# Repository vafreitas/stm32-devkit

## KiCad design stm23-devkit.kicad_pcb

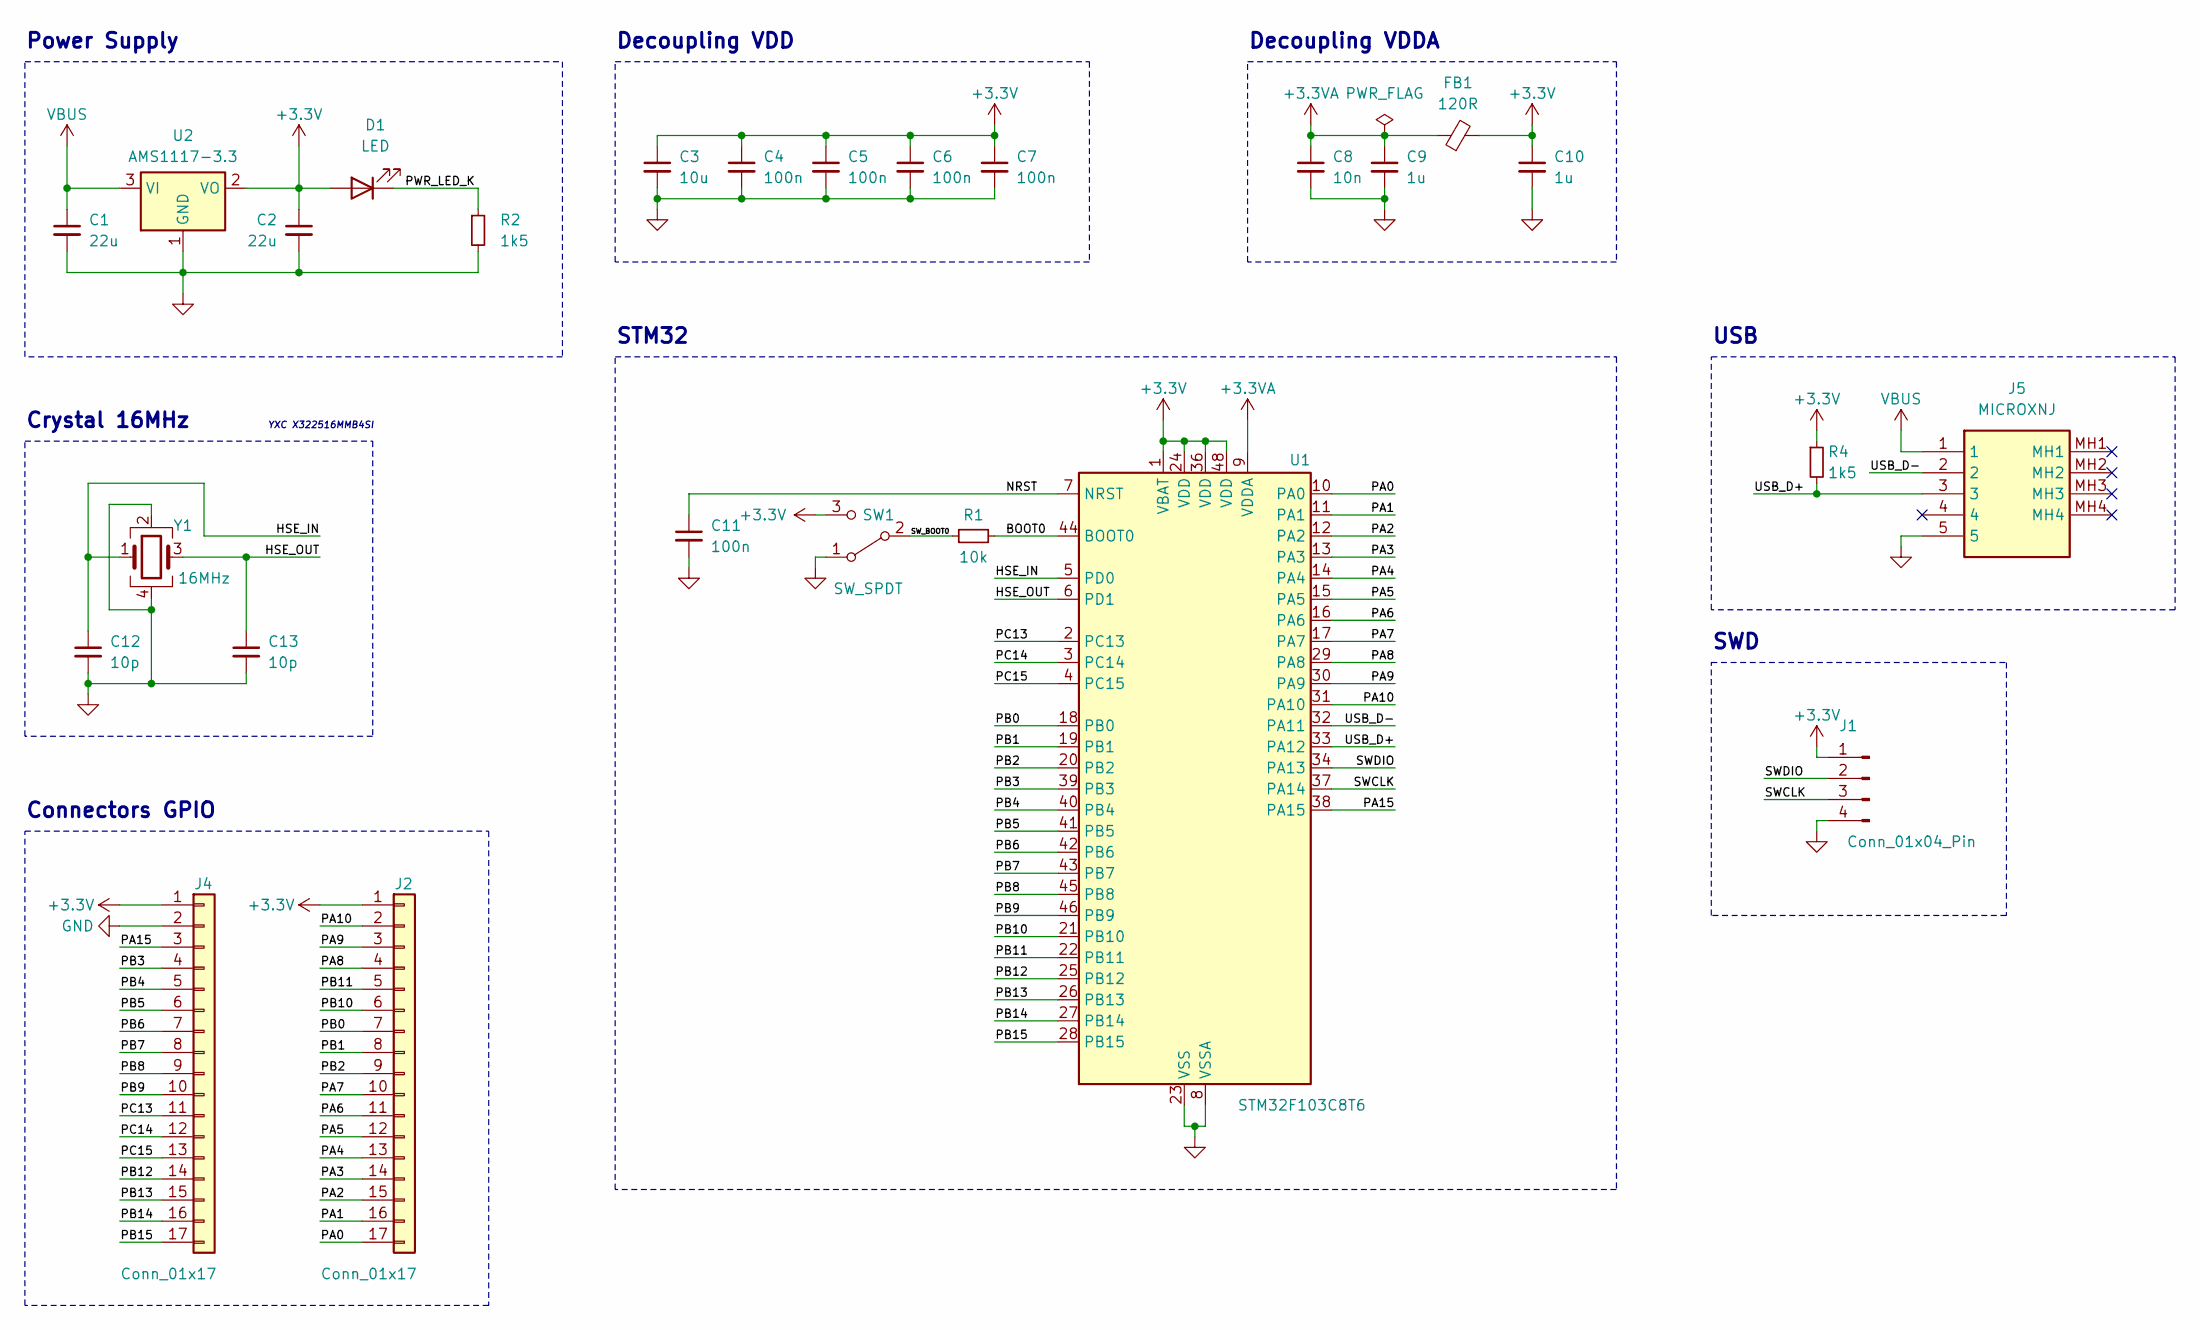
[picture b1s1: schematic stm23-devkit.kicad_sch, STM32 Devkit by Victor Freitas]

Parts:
C1, C2: 22u; C_0805_2012Metric
C3: 10u; C_0603_1608Metric
C4, C5, C6, C7, C11: 100n; C_0603_1608Metric
C8: 10n; C_0603_1608Metric
C9, C10: 1u; C_0603_1608Metric
C12, C13: 10p; C_0603_1608Metric
D1: LED; LED_0603_1608Metric
FB1: 120R; L_0603_1608Metric
J1: Conn_01x04_Pin; PinHeader_1x04_P2.54mm_Vertical
J2, J4: Conn_01x17; PinHeader_1x17_P2.54mm_Vertical
J5: MICROXNJ; Manufacturer_Part_Number MICROXNJ
R1: 10k; R_0603_1608Metric
R2, R4: 1k5; R_0603_1608Metric
SW1: SW_SPDT; SW_SPDT_PCM12
U1: STM32F103C8T6; LQFP-48_7x7mm_P0.5mm
U2: AMS1117-3.3; SOT-223-3_TabPin2
Y1: 16MHz; Crystal_SMD_3225-4Pin_3.2x2.5mm

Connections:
+3.3V: C2.1, C3.1, C4.1, C5.1, C6.1, C7.1, C10.1, D1.2 (A), FB1.2, J1.1, J2.1, J4.1, R4.1, SW1.3 (C), U1.1 (VBAT), U1.24 (VDD), U1.36 (VDD), U1.48 (VDD), U2.2 (VO)
+3.3VA: C8.1, C9.1, FB1.1, U1.9 (VDDA)
/BOOT0: R1.2, U1.44 (BOOT0)
/HSE_IN: C12.1, U1.5 (PD0), Y1.1
/HSE_OUT: C13.1, U1.6 (PD1), Y1.3
/NRST: C11.1, U1.7 (NRST)
/PA0: J2.17, U1.10 (PA0)
/PA1: J2.16, U1.11 (PA1)
/PA2: J2.15, U1.12 (PA2)
/PA3: J2.14, U1.13 (PA3)
/PA4: J2.13, U1.14 (PA4)
/PA5: J2.12, U1.15 (PA5)
/PA6: J2.11, U1.16 (PA6)
/PA7: J2.10, U1.17 (PA7)
/PA8: J2.4, U1.29 (PA8)
/PA9: J2.3, U1.30 (PA9)
/PA10: J2.2, U1.31 (PA10)
/PA15: J4.3, U1.38 (PA15)
/PB0: J2.7, U1.18 (PB0)
/PB1: J2.8, U1.19 (PB1)
/PB2: J2.9, U1.20 (PB2)
/PB3: J4.4, U1.39 (PB3)
/PB4: J4.5, U1.40 (PB4)
/PB5: J4.6, U1.41 (PB5)
/PB6: J4.7, U1.42 (PB6)
/PB7: J4.8, U1.43 (PB7)
/PB8: J4.9, U1.45 (PB8)
/PB9: J4.10, U1.46 (PB9)
/PB10: J2.6, U1.21 (PB10)
/PB11: J2.5, U1.22 (PB11)
/PB12: J4.14, U1.25 (PB12)
/PB13: J4.15, U1.26 (PB13)
/PB14: J4.16, U1.27 (PB14)
/PB15: J4.17, U1.28 (PB15)
/PC13: J4.11, U1.2 (PC13)
/PC14: J4.12, U1.3 (PC14)
/PC15: J4.13, U1.4 (PC15)
/PWR_LED_K: D1.1 (K), R2.1
/SWCLK: J1.3, U1.37 (PA14)
/SWDIO: J1.2, U1.34 (PA13)
/SW_BOOT0: R1.1, SW1.2 (B)
/USB_D+: J5.3, R4.2, U1.33 (PA12)
/USB_D-: J5.2, U1.32 (PA11)
GND: C1.2, C2.2, C3.2, C4.2, C5.2, C6.2, C7.2, C8.2, C9.2, C10.2, C11.2, C12.2, C13.2, J1.4, J4.2, J5.5, R2.2, SW1.1 (A), U1.8 (VSSA), U1.23 (VSS), U1.35 (VSS), U1.47 (VSS), U2.1 (GND), Y1.2, Y1.4
VBUS: C1.1, J5.1, U2.3 (VI)

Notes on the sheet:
STM32
Connectors GPIO
Decoupling VDD
Crystal 16MHz
SWD
Decoupling VDDA
Power Supply
USB
YXC X322516MMB4SI

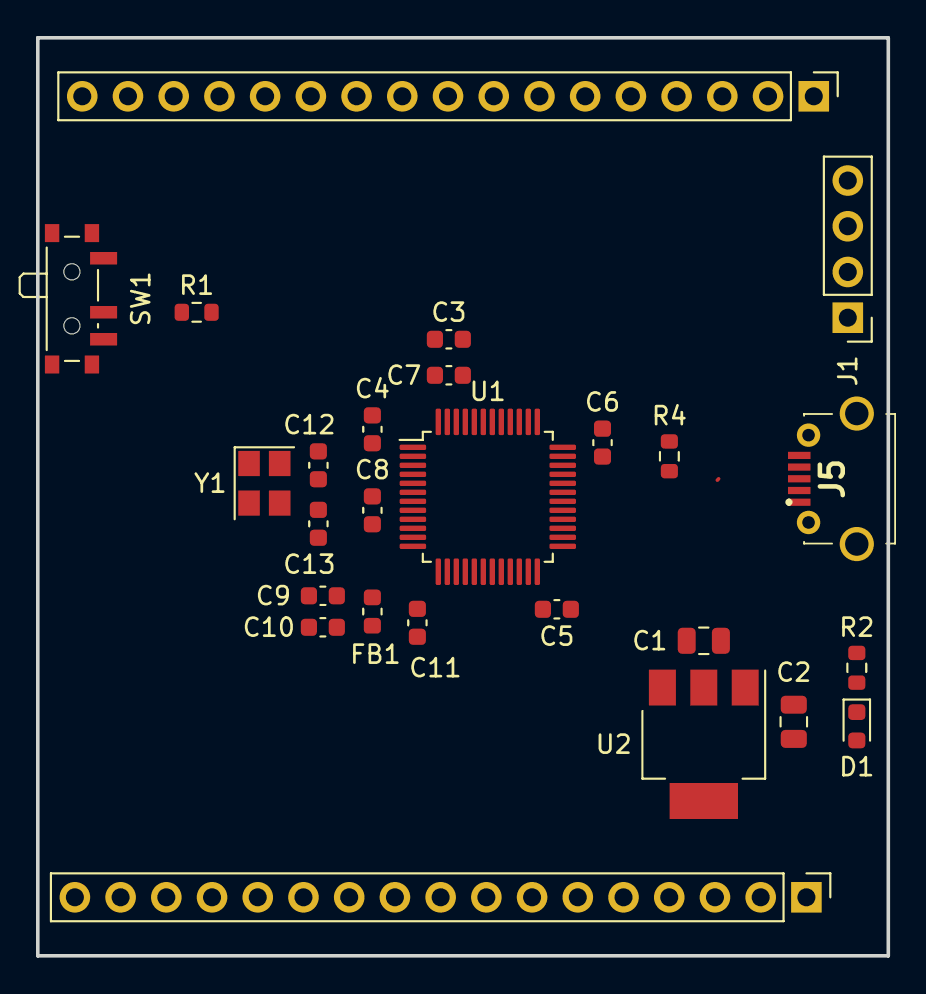
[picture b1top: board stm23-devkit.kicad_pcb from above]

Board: 2 copper layers, 47.2 x 51.0 mm, 26 parts (0 on the bottom side), 45 nets.

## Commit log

2023-08-20 Changes in schematic
2023-08-20 PCB created and organized
